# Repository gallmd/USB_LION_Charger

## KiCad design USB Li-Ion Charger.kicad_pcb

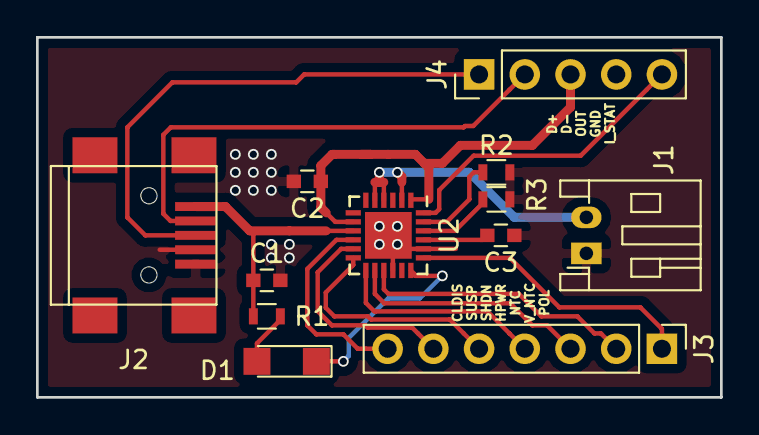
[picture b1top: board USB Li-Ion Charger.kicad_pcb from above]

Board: 2 copper layers, 38.0 x 20.0 mm, 12 parts (0 on the bottom side), 19 nets.

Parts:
C1, C2: 4.7uF; C_0603
C3: 0.1uF; C_0603
D1: LED; LED_1206
J1: CONN_01X02; JST_PH_S2B-PH-K_02x2.00mm_Angled
J2: USB_B; USB_Mini-B
J3: CONN_01X07; Pin_Header_Straight_1x07_Pitch2.54mm
J4: CONN_01X05; Pin_Header_Straight_1x05_Pitch2.54mm
R1: 330R; R_0603
R2: 100k; R_0603
R3: 2.1k; R_0603
U2: LTC4066; QFN-24-1EP_4x4mm_Pitch0.5mm

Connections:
/LTC_BAT: J1.2, U2.2, U2.4, U2.5
/LTC_IN: C1.1, J2.1, R1.1, U2.9
/LTC_OUT: C2.1, J4.3, U2.1, U2.3, U2.8
GND: C1.2, C2.2, C3.2, J1.1, J2.4, J2.5, J4.4, R2.1, R3.1, U2.16, U2.20, U2.25
LTC_CLDIS: J3.7, U2.10
LTC_CLPROG: R3.2, U2.22
LTC_HPWR: J3.4, U2.13
LTC_NTC: J3.3, U2.14
LTC_POL: J3.1, U2.19
LTC_PROG: R2.2, U2.23
LTC_SHDN: J3.5, U2.12
LTC_SUSP: J3.6, U2.11
LTC_TIMER: C3.1, U2.21
LTC_V_NTC: J3.2, U2.15
unnamed: D1.1, U2.18
unnamed: D1.2, R1.2
unnamed: J2.2, J4.2
unnamed: J2.3, J4.1
unnamed: J4.5, U2.24

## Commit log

2019-05-18 first commit before changing IC
